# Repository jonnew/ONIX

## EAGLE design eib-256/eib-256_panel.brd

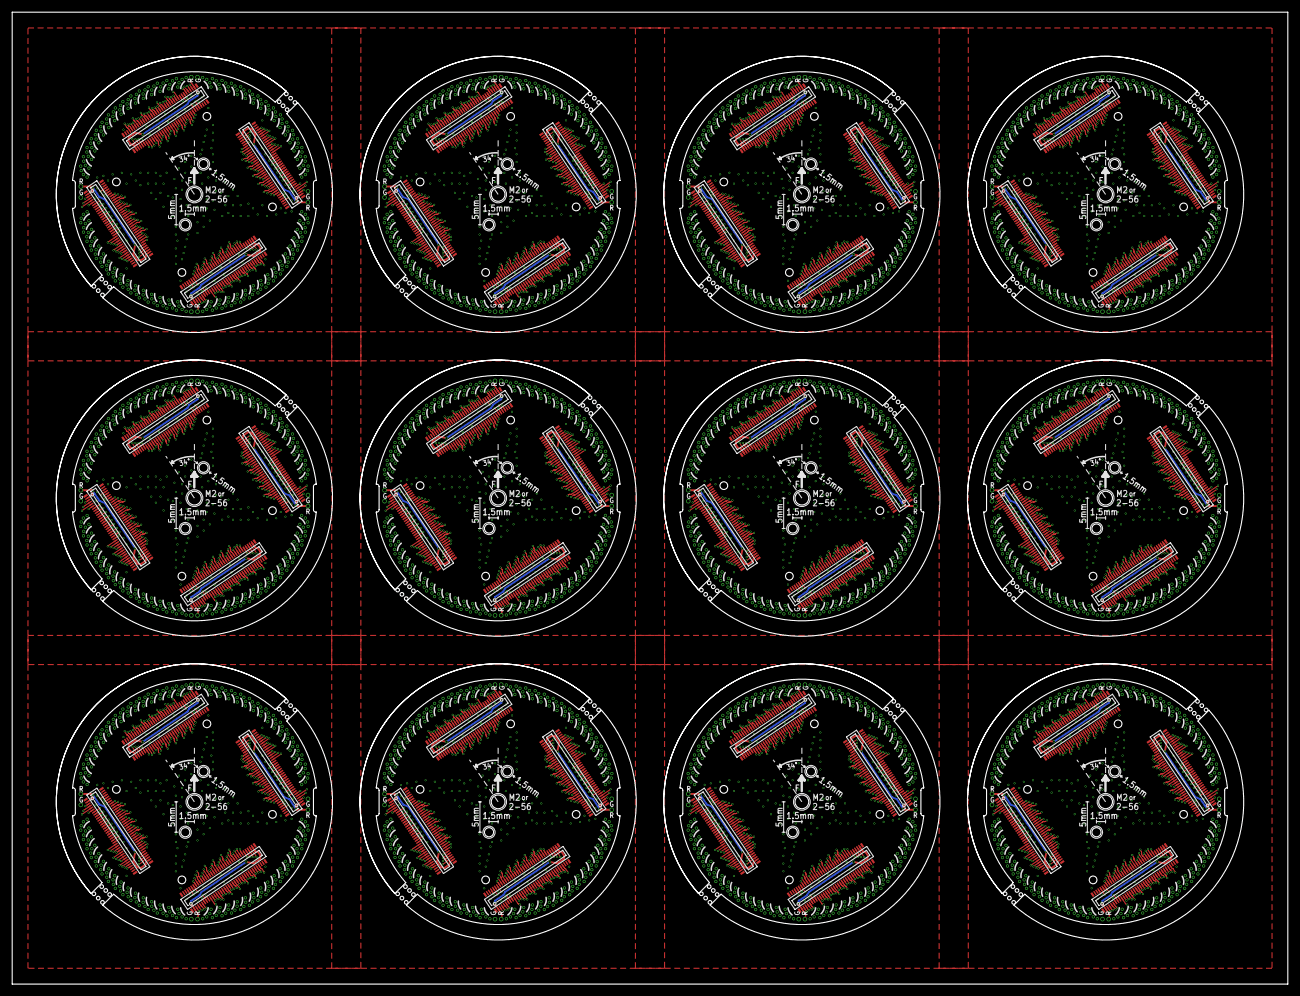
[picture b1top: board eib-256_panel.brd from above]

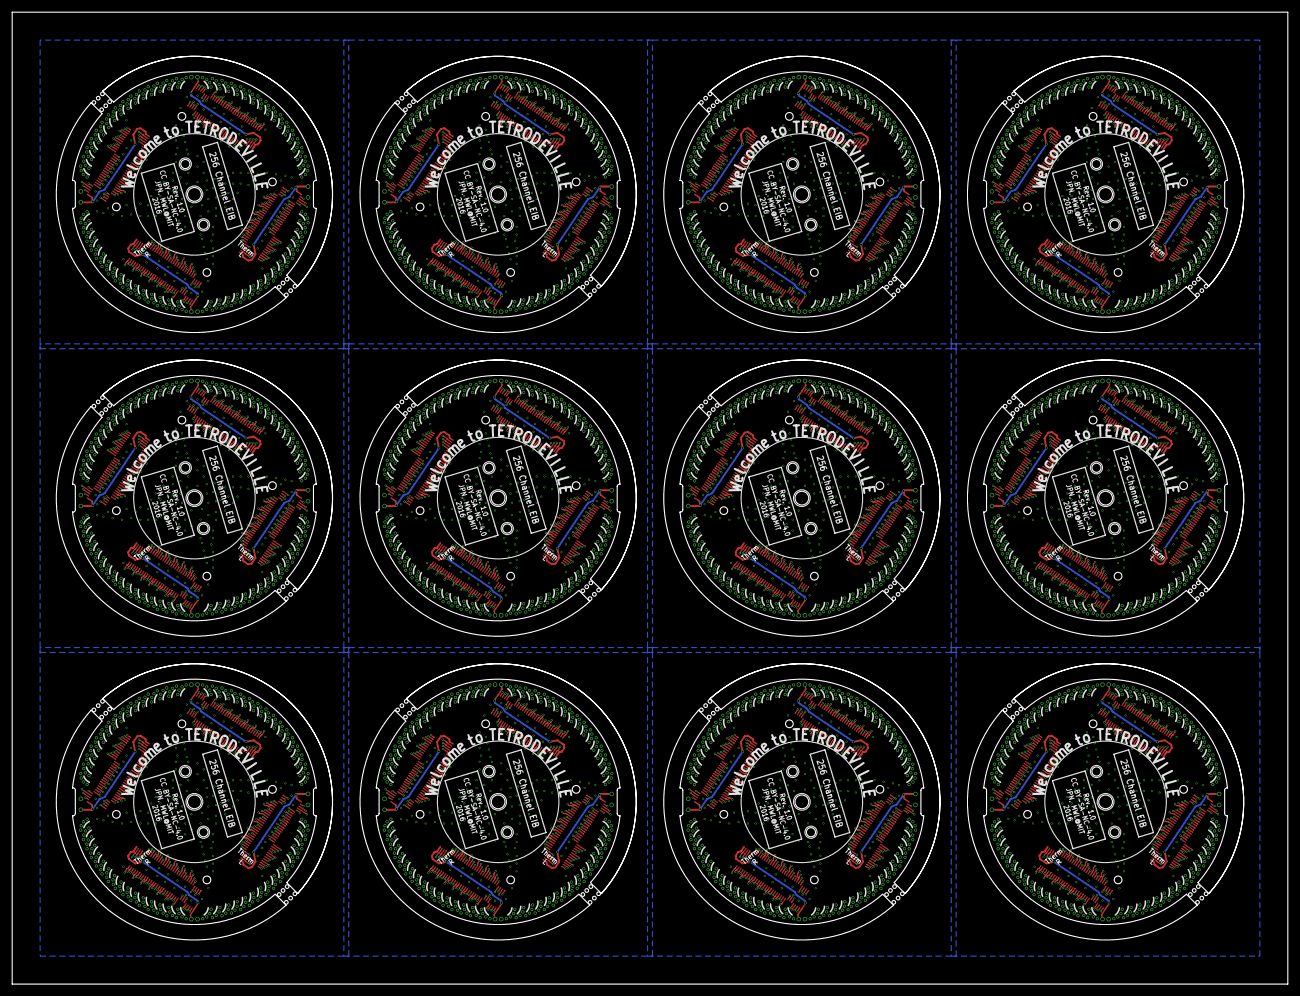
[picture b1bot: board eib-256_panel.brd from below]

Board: 4 copper layers, 210.0 x 160.0 mm, 924 parts (384 on the bottom side), 3132 nets.

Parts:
A, A1, A2, A3, A4, A5, A6, A7, A8, A9, A10, A11: DF40HEAD; DF40-70HEAD
AGND_A, AGND_A1, AGND_A2, AGND_A3, AGND_A4, AGND_A5, AGND_A6, AGND_A7, AGND_A8, AGND_A9, AGND_A10, AGND_A11: LRG_GP; GOLDPIN_0.5ID_0.7OD
AGND_B, AGND_B1, AGND_B2, AGND_B3, AGND_B4, AGND_B5, AGND_B6, AGND_B7, AGND_B8, AGND_B9, AGND_B10, AGND_B11: LRG_GP; GOLDPIN_0.5ID_0.7OD
B, B1, B2, B3, B4, B5, B6, B7, B8, B9, B10, B11: DF40HEAD; DF40-70HEAD
C, C1, C2, C3, C4, C5, C6, C7, C8, C9, C10, C11: DF40HEAD; DF40-70HEAD
D, D1, D2, D3, D4, D5, D6, D7, D8, D9, D10, D11: DF40HEAD; DF40-70HEAD
REF_A0, REF_A1, REF_A2, REF_A3, REF_A4, REF_A5, REF_A6, REF_A7, REF_A8, REF_A9, REF_A10, REF_A11: LRG_GP; GOLDPIN_0.5ID_0.7OD
REF_B, REF_B1, REF_B2, REF_B3, REF_B4, REF_B5, REF_B6, REF_B7, REF_B8, REF_B9, REF_B10, REF_B11: LRG_GP; GOLDPIN_0.5ID_0.7OD
REF_C, REF_C1, REF_C2, REF_C3, REF_C4, REF_C5, REF_C6, REF_C7, REF_C8, REF_C9, REF_C10, REF_C11: LRG_GP; GOLDPIN_0.5ID_0.7OD
REF_D, REF_D1, REF_D2, REF_D3, REF_D4, REF_D5, REF_D6, REF_D7, REF_D8, REF_D9, REF_D10, REF_D11: LRG_GP; GOLDPIN_0.5ID_0.7OD
SHLD_C, SHLD_C1, SHLD_C2, SHLD_C3, SHLD_C4, SHLD_C5, SHLD_C6, SHLD_C7, SHLD_C8, SHLD_C9, SHLD_C10, SHLD_C11: LRG_GP; GOLDPIN_0.5ID_0.7OD
SHLD_D, SHLD_D1, SHLD_D2, SHLD_D3, SHLD_D4, SHLD_D5, SHLD_D6, SHLD_D7, SHLD_D8, SHLD_D9, SHLD_D10, SHLD_D11: LRG_GP; GOLDPIN_0.5ID_0.7OD
TET0, TET64, TET128, TET192, TET256, TET320, TET384, TET448, TET512, TET576, TET640, TET704: 0; TETRODE_0.3ID_LINEAR
TET1, TET65, TET129, TET193, TET257, TET321, TET385, TET449, TET513, TET577, TET641, TET705: 1; TETRODE_0.3ID_LINEAR
TET2, TET66, TET130, TET194, TET258, TET322, TET386, TET450, TET514, TET578, TET642, TET706: 2; TETRODE_0.3ID_LINEAR
TET3, TET67, TET131, TET195, TET259, TET323, TET387, TET451, TET515, TET579, TET643, TET707: 3; TETRODE_0.3ID_LINEAR
TET4, TET68, TET132, TET196, TET260, TET324, TET388, TET452, TET516, TET580, TET644, TET708: 4; TETRODE_0.3ID_LINEAR
TET5, TET69, TET133, TET197, TET261, TET325, TET389, TET453, TET517, TET581, TET645, TET709: 5; TETRODE_0.3ID_LINEAR
TET6, TET70, TET134, TET198, TET262, TET326, TET390, TET454, TET518, TET582, TET646, TET710: 6; TETRODE_0.3ID_LINEAR
TET7, TET71, TET135, TET199, TET263, TET327, TET391, TET455, TET519, TET583, TET647, TET711: 7; TETRODE_0.3ID_LINEAR
TET8, TET72, TET136, TET200, TET264, TET328, TET392, TET456, TET520, TET584, TET648, TET712: 8; TETRODE_0.3ID_LINEAR
TET9, TET73, TET137, TET201, TET265, TET329, TET393, TET457, TET521, TET585, TET649, TET713: 9; TETRODE_0.3ID_LINEAR
TET10, TET74, TET138, TET202, TET266, TET330, TET394, TET458, TET522, TET586, TET650, TET714: 10; TETRODE_0.3ID_LINEAR
TET11, TET75, TET139, TET203, TET267, TET331, TET395, TET459, TET523, TET587, TET651, TET715: 11; TETRODE_0.3ID_LINEAR
TET12, TET76, TET140, TET204, TET268, TET332, TET396, TET460, TET524, TET588, TET652, TET716: 12; TETRODE_0.3ID_LINEAR
TET13, TET77, TET141, TET205, TET269, TET333, TET397, TET461, TET525, TET589, TET653, TET717: 13; TETRODE_0.3ID_LINEAR
TET14, TET78, TET142, TET206, TET270, TET334, TET398, TET462, TET526, TET590, TET654, TET718: 14; TETRODE_0.3ID_LINEAR
TET15, TET79, TET143, TET207, TET271, TET335, TET399, TET463, TET527, TET591, TET655, TET719: 15; TETRODE_0.3ID_LINEAR
TET16, TET112, TET176, TET240, TET304, TET368, TET432, TET496, TET560, TET624, TET688, TET752: 16; TETRODE_0.3ID_LINEAR
TET17, TET113, TET177, TET241, TET305, TET369, TET433, TET497, TET561, TET625, TET689, TET753: 17; TETRODE_0.3ID_LINEAR
TET18, TET114, TET178, TET242, TET306, TET370, TET434, TET498, TET562, TET626, TET690, TET754: 18; TETRODE_0.3ID_LINEAR
TET19, TET115, TET179, TET243, TET307, TET371, TET435, TET499, TET563, TET627, TET691, TET755: 19; TETRODE_0.3ID_LINEAR
TET20, TET116, TET180, TET244, TET308, TET372, TET436, TET500, TET564, TET628, TET692, TET756: 20; TETRODE_0.3ID_LINEAR
TET21, TET117, TET181, TET245, TET309, TET373, TET437, TET501, TET565, TET629, TET693, TET757: 21; TETRODE_0.3ID_LINEAR
TET22, TET118, TET182, TET246, TET310, TET374, TET438, TET502, TET566, TET630, TET694, TET758: 22; TETRODE_0.3ID_LINEAR
TET23, TET119, TET183, TET247, TET311, TET375, TET439, TET503, TET567, TET631, TET695, TET759: 23; TETRODE_0.3ID_LINEAR
TET24, TET120, TET184, TET248, TET312, TET376, TET440, TET504, TET568, TET632, TET696, TET760: 24; TETRODE_0.3ID_LINEAR
TET25, TET121, TET185, TET249, TET313, TET377, TET441, TET505, TET569, TET633, TET697, TET761: 25; TETRODE_0.3ID_LINEAR
TET26, TET122, TET186, TET250, TET314, TET378, TET442, TET506, TET570, TET634, TET698, TET762: 26; TETRODE_0.3ID_LINEAR
TET27, TET123, TET187, TET251, TET315, TET379, TET443, TET507, TET571, TET635, TET699, TET763: 27; TETRODE_0.3ID_LINEAR
TET28, TET124, TET188, TET252, TET316, TET380, TET444, TET508, TET572, TET636, TET700, TET764: 28; TETRODE_0.3ID_LINEAR
TET29, TET125, TET189, TET253, TET317, TET381, TET445, TET509, TET573, TET637, TET701, TET765: 29; TETRODE_0.3ID_LINEAR
TET30, TET126, TET190, TET254, TET318, TET382, TET446, TET510, TET574, TET638, TET702, TET766: 30; TETRODE_0.3ID_LINEAR
TET31, TET127, TET191, TET255, TET319, TET383, TET447, TET511, TET575, TET639, TET703, TET767: 31; TETRODE_0.3ID_LINEAR
TET32, TET96, TET160, TET224, TET288, TET352, TET416, TET480, TET544, TET608, TET672, TET736: 32; TETRODE_0.3ID_LINEAR
TET33, TET97, TET161, TET225, TET289, TET353, TET417, TET481, TET545, TET609, TET673, TET737: 33; TETRODE_0.3ID_LINEAR
TET34, TET98, TET162, TET226, TET290, TET354, TET418, TET482, TET546, TET610, TET674, TET738: 34; TETRODE_0.3ID_LINEAR
TET35, TET99, TET163, TET227, TET291, TET355, TET419, TET483, TET547, TET611, TET675, TET739: 35; TETRODE_0.3ID_LINEAR
TET36, TET100, TET164, TET228, TET292, TET356, TET420, TET484, TET548, TET612, TET676, TET740: 36; TETRODE_0.3ID_LINEAR
TET37, TET101, TET165, TET229, TET293, TET357, TET421, TET485, TET549, TET613, TET677, TET741: 37; TETRODE_0.3ID_LINEAR
TET38, TET102, TET166, TET230, TET294, TET358, TET422, TET486, TET550, TET614, TET678, TET742: 38; TETRODE_0.3ID_LINEAR
TET39, TET103, TET167, TET231, TET295, TET359, TET423, TET487, TET551, TET615, TET679, TET743: 39; TETRODE_0.3ID_LINEAR
TET40, TET104, TET168, TET232, TET296, TET360, TET424, TET488, TET552, TET616, TET680, TET744: 40; TETRODE_0.3ID_LINEAR
TET41, TET105, TET169, TET233, TET297, TET361, TET425, TET489, TET553, TET617, TET681, TET745: 41; TETRODE_0.3ID_LINEAR
TET42, TET106, TET170, TET234, TET298, TET362, TET426, TET490, TET554, TET618, TET682, TET746: 42; TETRODE_0.3ID_LINEAR
TET43, TET107, TET171, TET235, TET299, TET363, TET427, TET491, TET555, TET619, TET683, TET747: 43; TETRODE_0.3ID_LINEAR
TET44, TET108, TET172, TET236, TET300, TET364, TET428, TET492, TET556, TET620, TET684, TET748: 44; TETRODE_0.3ID_LINEAR
TET45, TET109, TET173, TET237, TET301, TET365, TET429, TET493, TET557, TET621, TET685, TET749: 45; TETRODE_0.3ID_LINEAR
TET46, TET110, TET174, TET238, TET302, TET366, TET430, TET494, TET558, TET622, TET686, TET750: 46; TETRODE_0.3ID_LINEAR
TET47, TET111, TET175, TET239, TET303, TET367, TET431, TET495, TET559, TET623, TET687, TET751: 47; TETRODE_0.3ID_LINEAR
TET48, TET80, TET144, TET208, TET272, TET336, TET400, TET464, TET528, TET592, TET656, TET720: 48; TETRODE_0.3ID_LINEAR
TET49, TET81, TET145, TET209, TET273, TET337, TET401, TET465, TET529, TET593, TET657, TET721: 49; TETRODE_0.3ID_LINEAR
TET50, TET82, TET146, TET210, TET274, TET338, TET402, TET466, TET530, TET594, TET658, TET722: 50; TETRODE_0.3ID_LINEAR
TET51, TET83, TET147, TET211, TET275, TET339, TET403, TET467, TET531, TET595, TET659, TET723: 51; TETRODE_0.3ID_LINEAR
TET52, TET84, TET148, TET212, TET276, TET340, TET404, TET468, TET532, TET596, TET660, TET724: 52; TETRODE_0.3ID_LINEAR
TET53, TET85, TET149, TET213, TET277, TET341, TET405, TET469, TET533, TET597, TET661, TET725: 53; TETRODE_0.3ID_LINEAR
TET54, TET86, TET150, TET214, TET278, TET342, TET406, TET470, TET534, TET598, TET662, TET726: 54; TETRODE_0.3ID_LINEAR
TET55, TET87, TET151, TET215, TET279, TET343, TET407, TET471, TET535, TET599, TET663, TET727: 55; TETRODE_0.3ID_LINEAR
TET56, TET88, TET152, TET216, TET280, TET344, TET408, TET472, TET536, TET600, TET664, TET728: 56; TETRODE_0.3ID_LINEAR
TET57, TET89, TET153, TET217, TET281, TET345, TET409, TET473, TET537, TET601, TET665, TET729: 57; TETRODE_0.3ID_LINEAR
TET58, TET90, TET154, TET218, TET282, TET346, TET410, TET474, TET538, TET602, TET666, TET730: 58; TETRODE_0.3ID_LINEAR
TET59, TET91, TET155, TET219, TET283, TET347, TET411, TET475, TET539, TET603, TET667, TET731: 59; TETRODE_0.3ID_LINEAR
TET60, TET92, TET156, TET220, TET284, TET348, TET412, TET476, TET540, TET604, TET668, TET732: 60; TETRODE_0.3ID_LINEAR
TET61, TET93, TET157, TET221, TET285, TET349, TET413, TET477, TET541, TET605, TET669, TET733: 61; TETRODE_0.3ID_LINEAR
TET62, TET94, TET158, TET222, TET286, TET350, TET414, TET478, TET542, TET606, TET670, TET734: 62; TETRODE_0.3ID_LINEAR
TET63, TET95, TET159, TET223, TET287, TET351, TET415, TET479, TET543, TET607, TET671, TET735: 63; TETRODE_0.3ID_LINEAR
U$1, U$2, U$3, U$4, U$5, U$6, U$7, U$8, U$9, U$10, U$11, U$12: EIB_MOUNT_A

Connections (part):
GND: A.34, A.35, A.69, A.70, A.M1, A.M2, A.M3, A.M4, AGND_A.P$1, AGND_B.P$1, B.34, B.35, B.69, B.70, B.M1, B.M2, B.M3, B.M4, C.34, C.35, C.69, C.70, C.M1, C.M2, C.M3, C.M4, D.34, D.35, D.69, D.70, D.M1, D.M2, D.M3, D.M4, SHLD_C.P$1, SHLD_D.P$1
GND1: A1.34, A1.35, A1.69, A1.70, A1.M1, A1.M2, A1.M3, A1.M4, AGND_A1.P$1, AGND_B1.P$1, B1.34, B1.35, B1.69, B1.70, B1.M1, B1.M2, B1.M3, B1.M4, C1.34, C1.35, C1.69, C1.70, C1.M1, C1.M2, C1.M3, C1.M4, D1.34, D1.35, D1.69, D1.70, D1.M1, D1.M2, D1.M3, D1.M4, SHLD_C1.P$1, SHLD_D1.P$1
GND2: A2.34, A2.35, A2.69, A2.70, A2.M1, A2.M2, A2.M3, A2.M4, AGND_A2.P$1, AGND_B2.P$1, B2.34, B2.35, B2.69, B2.70, B2.M1, B2.M2, B2.M3, B2.M4, C2.34, C2.35, C2.69, C2.70, C2.M1, C2.M2, C2.M3, C2.M4, D2.34, D2.35, D2.69, D2.70, D2.M1, D2.M2, D2.M3, D2.M4, SHLD_C2.P$1, SHLD_D2.P$1
GND3: A3.34, A3.35, A3.69, A3.70, A3.M1, A3.M2, A3.M3, A3.M4, AGND_A3.P$1, AGND_B3.P$1, B3.34, B3.35, B3.69, B3.70, B3.M1, B3.M2, B3.M3, B3.M4, C3.34, C3.35, C3.69, C3.70, C3.M1, C3.M2, C3.M3, C3.M4, D3.34, D3.35, D3.69, D3.70, D3.M1, D3.M2, D3.M3, D3.M4, SHLD_C3.P$1, SHLD_D3.P$1
GND4: A4.34, A4.35, A4.69, A4.70, A4.M1, A4.M2, A4.M3, A4.M4, AGND_A4.P$1, AGND_B4.P$1, B4.34, B4.35, B4.69, B4.70, B4.M1, B4.M2, B4.M3, B4.M4, C4.34, C4.35, C4.69, C4.70, C4.M1, C4.M2, C4.M3, C4.M4, D4.34, D4.35, D4.69, D4.70, D4.M1, D4.M2, D4.M3, D4.M4, SHLD_C4.P$1, SHLD_D4.P$1
GND5: A5.34, A5.35, A5.69, A5.70, A5.M1, A5.M2, A5.M3, A5.M4, AGND_A5.P$1, AGND_B5.P$1, B5.34, B5.35, B5.69, B5.70, B5.M1, B5.M2, B5.M3, B5.M4, C5.34, C5.35, C5.69, C5.70, C5.M1, C5.M2, C5.M3, C5.M4, D5.34, D5.35, D5.69, D5.70, D5.M1, D5.M2, D5.M3, D5.M4, SHLD_C5.P$1, SHLD_D5.P$1
GND6: A6.34, A6.35, A6.69, A6.70, A6.M1, A6.M2, A6.M3, A6.M4, AGND_A6.P$1, AGND_B6.P$1, B6.34, B6.35, B6.69, B6.70, B6.M1, B6.M2, B6.M3, B6.M4, C6.34, C6.35, C6.69, C6.70, C6.M1, C6.M2, C6.M3, C6.M4, D6.34, D6.35, D6.69, D6.70, D6.M1, D6.M2, D6.M3, D6.M4, SHLD_C6.P$1, SHLD_D6.P$1
GND7: A7.34, A7.35, A7.69, A7.70, A7.M1, A7.M2, A7.M3, A7.M4, AGND_A7.P$1, AGND_B7.P$1, B7.34, B7.35, B7.69, B7.70, B7.M1, B7.M2, B7.M3, B7.M4, C7.34, C7.35, C7.69, C7.70, C7.M1, C7.M2, C7.M3, C7.M4, D7.34, D7.35, D7.69, D7.70, D7.M1, D7.M2, D7.M3, D7.M4, SHLD_C7.P$1, SHLD_D7.P$1
GND8: A8.34, A8.35, A8.69, A8.70, A8.M1, A8.M2, A8.M3, A8.M4, AGND_A8.P$1, AGND_B8.P$1, B8.34, B8.35, B8.69, B8.70, B8.M1, B8.M2, B8.M3, B8.M4, C8.34, C8.35, C8.69, C8.70, C8.M1, C8.M2, C8.M3, C8.M4, D8.34, D8.35, D8.69, D8.70, D8.M1, D8.M2, D8.M3, D8.M4, SHLD_C8.P$1, SHLD_D8.P$1
GND9: A9.34, A9.35, A9.69, A9.70, A9.M1, A9.M2, A9.M3, A9.M4, AGND_A9.P$1, AGND_B9.P$1, B9.34, B9.35, B9.69, B9.70, B9.M1, B9.M2, B9.M3, B9.M4, C9.34, C9.35, C9.69, C9.70, C9.M1, C9.M2, C9.M3, C9.M4, D9.34, D9.35, D9.69, D9.70, D9.M1, D9.M2, D9.M3, D9.M4, SHLD_C9.P$1, SHLD_D9.P$1
GND10: A10.34, A10.35, A10.69, A10.70, A10.M1, A10.M2, A10.M3, A10.M4, AGND_A10.P$1, AGND_B10.P$1, B10.34, B10.35, B10.69, B10.70, B10.M1, B10.M2, B10.M3, B10.M4, C10.34, C10.35, C10.69, C10.70, C10.M1, C10.M2, C10.M3, C10.M4, D10.34, D10.35, D10.69, D10.70, D10.M1, D10.M2, D10.M3, D10.M4, SHLD_C10.P$1, SHLD_D10.P$1
GND11: A11.34, A11.35, A11.69, A11.70, A11.M1, A11.M2, A11.M3, A11.M4, AGND_A11.P$1, AGND_B11.P$1, B11.34, B11.35, B11.69, B11.70, B11.M1, B11.M2, B11.M3, B11.M4, C11.34, C11.35, C11.69, C11.70, C11.M1, C11.M2, C11.M3, C11.M4, D11.34, D11.35, D11.69, D11.70, D11.M1, D11.M2, D11.M3, D11.M4, SHLD_C11.P$1, SHLD_D11.P$1
unnamed: D.2, TET48.0
unnamed: D.3, TET48.1
unnamed: D.4, TET48.2
unnamed: D.5, TET48.3
unnamed: D.6, TET49.0
unnamed: D.7, TET49.1
unnamed: D.8, TET49.2
unnamed: D.9, TET49.3
unnamed: D.10, TET50.0
unnamed: D.11, TET50.1
unnamed: D.12, TET50.2
unnamed: D.13, TET50.3
unnamed: D.14, TET51.0
unnamed: D.15, TET51.1
unnamed: D.16, TET51.2
unnamed: D.17, TET51.3
unnamed: D.18, TET52.0
unnamed: D.19, TET52.1
unnamed: D.20, TET52.2
unnamed: D.21, TET52.3
unnamed: D.22, TET53.0
unnamed: D.23, TET53.1
unnamed: D.24, TET53.2
unnamed: D.25, TET53.3
unnamed: D.26, TET54.0
unnamed: D.27, TET54.1
unnamed: D.28, TET54.2
unnamed: D.29, TET54.3
unnamed: D.30, TET55.0
unnamed: D.31, TET55.1
unnamed: D.32, TET55.2
unnamed: D.42, TET57.1
unnamed: D.43, TET57.2
unnamed: D.44, TET57.3
unnamed: D.45, TET58.0
unnamed: D.46, TET58.1
unnamed: D.47, TET58.2
unnamed: D.48, TET58.3
unnamed: D.49, TET59.0
unnamed: D.50, TET59.1
unnamed: D.51, TET59.2
unnamed: D.52, TET59.3
unnamed: D.53, TET60.0
unnamed: D.54, TET60.1
unnamed: D.55, TET60.2
unnamed: D.56, TET60.3
unnamed: D.57, TET61.0
unnamed: D.58, TET61.1
unnamed: D.59, TET61.2
unnamed: D.60, TET61.3
unnamed: D.61, TET62.0
unnamed: D.62, TET62.1
unnamed: D.63, TET62.2
unnamed: D.64, TET62.3
unnamed: D.65, TET63.0
unnamed: D.66, TET63.1
unnamed: D.67, TET63.2
unnamed: D.68, TET63.3
unnamed: D.41, TET57.0
unnamed: D.40, TET56.3
unnamed: D.39, TET56.2
unnamed: D.38, TET56.1
unnamed: D.33, TET55.3
unnamed: D.37, TET56.0
unnamed: C.3, TET16.1
unnamed: C.2, TET16.0
unnamed: C.32, TET23.2
unnamed: C.33, TET23.3
unnamed: C.28, TET22.2
unnamed: C.29, TET22.3
unnamed: C.24, TET21.2
unnamed: C.25, TET21.3
unnamed: C.20, TET20.2
unnamed: C.21, TET20.3
unnamed: C.16, TET19.2
unnamed: C.17, TET19.3
unnamed: C.12, TET18.2
unnamed: C.13, TET18.3
unnamed: C.8, TET17.2
unnamed: C.9, TET17.3
unnamed: C.66, TET31.1
unnamed: C.65, TET31.0
unnamed: C.62, TET30.1
unnamed: C.64, TET30.3
unnamed: C.58, TET29.1
unnamed: C.57, TET29.0
unnamed: C.54, TET28.1
unnamed: C.53, TET28.0
unnamed: C.49, TET27.0
unnamed: C.50, TET27.1
unnamed: C.46, TET26.1
unnamed: C.45, TET26.0
unnamed: C.42, TET25.1
unnamed: C.41, TET25.0
unnamed: C.38, TET24.1
unnamed: C.37, TET24.0
unnamed: A1.33, TET71.0
unnamed: A1.32, TET71.1
unnamed: A1.31, TET71.2
unnamed: A1.30, TET71.3
unnamed: A1.29, TET70.0
unnamed: A1.28, TET70.1
unnamed: A1.27, TET70.2
unnamed: A1.26, TET70.3
unnamed: A1.25, TET69.0
unnamed: A1.24, TET69.1
unnamed: A1.23, TET69.2
unnamed: A1.22, TET69.3
unnamed: A1.21, TET68.0
unnamed: A1.20, TET68.1
unnamed: A1.19, TET68.2
unnamed: A1.18, TET68.3
unnamed: A1.17, TET67.0
unnamed: A1.16, TET67.1
unnamed: A1.15, TET67.2
unnamed: A1.14, TET67.3
unnamed: A1.13, TET66.0
unnamed: A1.12, TET66.1
unnamed: A1.11, TET66.2
unnamed: A1.10, TET66.3
unnamed: A1.9, TET65.0
unnamed: A1.8, TET65.1
unnamed: A1.7, TET65.2
unnamed: A1.6, TET65.3
unnamed: A1.5, TET64.0
unnamed: A1.4, TET64.1
unnamed: A1.3, TET64.2
unnamed: A1.38, TET72.2
unnamed: A1.39, TET72.1
unnamed: A1.40, TET72.0
unnamed: A1.41, TET73.3
unnamed: A1.42, TET73.2
unnamed: A1.43, TET73.1
unnamed: A1.44, TET73.0
unnamed: A1.45, TET74.3
unnamed: A1.46, TET74.2
unnamed: A1.47, TET74.1
unnamed: A1.48, TET74.0
unnamed: A1.49, TET75.3
unnamed: A1.50, TET75.2
unnamed: A1.51, TET75.1
unnamed: A1.52, TET75.0
unnamed: A1.53, TET76.3
unnamed: A1.54, TET76.2
unnamed: A1.55, TET76.1
unnamed: A1.56, TET76.0
unnamed: A1.57, TET77.3
unnamed: A1.58, TET77.2
unnamed: A1.59, TET77.1
unnamed: A1.60, TET77.0
unnamed: A1.61, TET78.3
unnamed: A1.62, TET78.2
unnamed: A1.63, TET78.1
unnamed: A1.64, TET78.0
unnamed: A1.65, TET79.3
unnamed: A1.66, TET79.2
unnamed: A1.67, TET79.1
unnamed: A1.68, TET79.0
unnamed: A1.2, TET64.3
unnamed: A1.37, TET72.3
unnamed: D1.2, TET80.0
unnamed: D1.3, TET80.1
unnamed: D1.4, TET80.2
unnamed: D1.5, TET80.3
unnamed: D1.6, TET81.0
unnamed: D1.7, TET81.1
unnamed: D1.8, TET81.2
unnamed: D1.9, TET81.3
unnamed: D1.10, TET82.0
unnamed: D1.11, TET82.1
unnamed: D1.12, TET82.2
unnamed: D1.13, TET82.3
unnamed: D1.14, TET83.0
unnamed: D1.15, TET83.1
unnamed: D1.16, TET83.2
unnamed: D1.17, TET83.3
unnamed: D1.18, TET84.0
unnamed: D1.19, TET84.1
unnamed: D1.20, TET84.2
unnamed: D1.21, TET84.3
unnamed: D1.22, TET85.0
unnamed: D1.23, TET85.1
unnamed: D1.24, TET85.2
unnamed: D1.25, TET85.3
unnamed: D1.26, TET86.0
unnamed: D1.27, TET86.1
unnamed: D1.28, TET86.2
unnamed: D1.29, TET86.3
unnamed: D1.30, TET87.0
unnamed: D1.31, TET87.1
unnamed: D1.32, TET87.2
unnamed: D1.33, TET87.3
unnamed: B.33, TET39.0
unnamed: B.32, TET39.1
unnamed: B.31, TET39.2
unnamed: B.30, TET39.3
unnamed: B.29, TET38.0
unnamed: B.28, TET38.1
unnamed: A.33, TET7.0
unnamed: A.32, TET7.1
unnamed: A.31, TET7.2
unnamed: A.30, TET7.3
unnamed: A.29, TET6.0
unnamed: A.28, TET6.1
unnamed: A.27, TET6.2
unnamed: A.26, TET6.3
unnamed: A.25, TET5.0
unnamed: A.24, TET5.1
unnamed: A.23, TET5.2
unnamed: A.22, TET5.3
unnamed: A.21, TET4.0
unnamed: A.20, TET4.1
unnamed: A.19, TET4.2
unnamed: A.18, TET4.3
unnamed: A.17, TET3.0
unnamed: A.16, TET3.1
unnamed: A.15, TET3.2
unnamed: A.14, TET3.3
unnamed: A.13, TET2.0
unnamed: A.12, TET2.1
unnamed: A.11, TET2.2
unnamed: A.10, TET2.3
unnamed: A.9, TET1.0
unnamed: A.8, TET1.1
unnamed: A.7, TET1.2
unnamed: A.6, TET1.3
unnamed: A.5, TET0.0
unnamed: A.4, TET0.1
unnamed: A.3, TET0.2
unnamed: A.2, TET0.3
unnamed: A.38, TET8.2
unnamed: A.39, TET8.1
unnamed: A.40, TET8.0
unnamed: A.41, TET9.3
unnamed: A.42, TET9.2
unnamed: A.43, TET9.1
unnamed: A.44, TET9.0
unnamed: A.45, TET10.3
unnamed: A.46, TET10.2
unnamed: A.47, TET10.1
unnamed: A.48, TET10.0
unnamed: A.49, TET11.3
unnamed: A.50, TET11.2
unnamed: A.51, TET11.1
unnamed: A.52, TET11.0
unnamed: A.53, TET12.3
unnamed: A.54, TET12.2
unnamed: A.55, TET12.1
unnamed: A.56, TET12.0
unnamed: A.57, TET13.3
unnamed: A.58, TET13.2
unnamed: A.59, TET13.1
unnamed: A.60, TET13.0
unnamed: A.61, TET14.3
unnamed: A.62, TET14.2
unnamed: A.63, TET14.1
unnamed: A.64, TET14.0
unnamed: A.65, TET15.3
unnamed: A.66, TET15.2
unnamed: A.67, TET15.1
unnamed: A.68, TET15.0
unnamed: B.27, TET38.2
unnamed: B.26, TET38.3
unnamed: B.25, TET37.0
unnamed: B.24, TET37.1
unnamed: B.23, TET37.2
unnamed: B.22, TET37.3
unnamed: B.21, TET36.0
unnamed: B.20, TET36.1
unnamed: B.19, TET36.2
unnamed: B.18, TET36.3
unnamed: B.17, TET35.0
unnamed: B.16, TET35.1
unnamed: B.15, TET35.2
unnamed: B.14, TET35.3
unnamed: B.13, TET34.0
unnamed: B.12, TET34.1
unnamed: B.11, TET34.2
unnamed: B.10, TET34.3
unnamed: B.9, TET33.0
unnamed: B.8, TET33.1
unnamed: B.7, TET33.2
unnamed: B.6, TET33.3
unnamed: B.5, TET32.0
unnamed: B.4, TET32.1
unnamed: B.3, TET32.2
unnamed: B.38, TET40.2
unnamed: B.39, TET40.1
unnamed: B.40, TET40.0
unnamed: B.41, TET41.3
unnamed: B.42, TET41.2
unnamed: B.43, TET41.1
unnamed: B.44, TET41.0
unnamed: B.45, TET42.3
unnamed: B.46, TET42.2
unnamed: B.47, TET42.1
unnamed: B.48, TET42.0
unnamed: B.49, TET43.3
unnamed: B.50, TET43.2
unnamed: B.51, TET43.1
unnamed: B.52, TET43.0
unnamed: B.53, TET44.3
unnamed: B.54, TET44.2
unnamed: B.55, TET44.1
unnamed: B.56, TET44.0
unnamed: B.57, TET45.3
unnamed: B.58, TET45.2
unnamed: B.59, TET45.1
unnamed: B.60, TET45.0
unnamed: B.61, TET46.3
unnamed: B.62, TET46.2
unnamed: B.63, TET46.1
unnamed: B.64, TET46.0
unnamed: B.65, TET47.3
unnamed: B.66, TET47.2
unnamed: B.67, TET47.1
unnamed: B.68, TET47.0
unnamed: B.2, TET32.3
unnamed: B.37, TET40.3
unnamed: D1.43, TET89.2
unnamed: D1.44, TET89.3
unnamed: C.4, TET16.2
unnamed: C.5, TET16.3
unnamed: C.6, TET17.0
unnamed: D1.45, TET90.0
unnamed: C.7, TET17.1
unnamed: D1.46, TET90.1
unnamed: C.10, TET18.0
unnamed: D1.47, TET90.2
unnamed: C.11, TET18.1
unnamed: D1.48, TET90.3
unnamed: C.14, TET19.0
unnamed: D1.49, TET91.0
unnamed: C.15, TET19.1
unnamed: D1.50, TET91.1
unnamed: C.18, TET20.0
unnamed: D1.51, TET91.2
unnamed: C.19, TET20.1
unnamed: D1.52, TET91.3
unnamed: C.22, TET21.0
unnamed: C.23, TET21.1
unnamed: D1.53, TET92.0
unnamed: D1.54, TET92.1
unnamed: D1.55, TET92.2
unnamed: C.27, TET22.1
unnamed: D1.56, TET92.3
unnamed: C.26, TET22.0
unnamed: C.30, TET23.0
unnamed: D1.57, TET93.0
unnamed: C.31, TET23.1
unnamed: D1.58, TET93.1
unnamed: C.43, TET25.2
unnamed: D1.59, TET93.2
unnamed: C.48, TET26.3
unnamed: D1.60, TET93.3
unnamed: C.47, TET26.2
unnamed: D1.61, TET94.0
unnamed: C.52, TET27.3
unnamed: D1.62, TET94.1
unnamed: C.51, TET27.2
unnamed: D1.63, TET94.2
unnamed: C.56, TET28.3
unnamed: D1.64, TET94.3
unnamed: C.55, TET28.2
unnamed: D1.65, TET95.0
unnamed: C.60, TET29.3
unnamed: D1.66, TET95.1
unnamed: C.59, TET29.2
unnamed: D1.67, TET95.2
unnamed: C.61, TET30.0
unnamed: D1.68, TET95.3
unnamed: C.63, TET30.2
unnamed: D1.42, TET89.1
unnamed: C.68, TET31.3
unnamed: D1.41, TET89.0
unnamed: C.67, TET31.2
unnamed: D1.40, TET88.3
unnamed: D1.39, TET88.2
unnamed: C.44, TET25.3
unnamed: D1.38, TET88.1
unnamed: D1.37, TET88.0
unnamed: C.39, TET24.2
unnamed: C.40, TET24.3
unnamed: B1.33, TET103.0
unnamed: B1.32, TET103.1
unnamed: B1.31, TET103.2
unnamed: B1.30, TET103.3
unnamed: B1.29, TET102.0
unnamed: B1.28, TET102.1
unnamed: B1.27, TET102.2
unnamed: B1.26, TET102.3
unnamed: B1.25, TET101.0
unnamed: B1.24, TET101.1
unnamed: B1.23, TET101.2
unnamed: B1.22, TET101.3
unnamed: B1.21, TET100.0
unnamed: B1.20, TET100.1
unnamed: B1.19, TET100.2
unnamed: B1.18, TET100.3
unnamed: B1.17, TET99.0
unnamed: B1.16, TET99.1
unnamed: B1.15, TET99.2
unnamed: B1.14, TET99.3
unnamed: B1.13, TET98.0
unnamed: B1.12, TET98.1
unnamed: B1.11, TET98.2
unnamed: B1.10, TET98.3
unnamed: B1.9, TET97.0
unnamed: B1.8, TET97.1
unnamed: B1.7, TET97.2
unnamed: B1.6, TET97.3
unnamed: B1.5, TET96.0
unnamed: B1.4, TET96.1
unnamed: B1.3, TET96.2
unnamed: B1.38, TET104.2
unnamed: B1.39, TET104.1
unnamed: B1.40, TET104.0
unnamed: B1.41, TET105.3
unnamed: B1.42, TET105.2
unnamed: B1.43, TET105.1
unnamed: B1.44, TET105.0
unnamed: B1.45, TET106.3
unnamed: B1.46, TET106.2
unnamed: B1.47, TET106.1
unnamed: B1.48, TET106.0
unnamed: B1.49, TET107.3
unnamed: B1.50, TET107.2
unnamed: B1.51, TET107.1
unnamed: B1.52, TET107.0
unnamed: B1.53, TET108.3
unnamed: B1.54, TET108.2
unnamed: B1.55, TET108.1
unnamed: B1.56, TET108.0
unnamed: B1.57, TET109.3
unnamed: B1.58, TET109.2
unnamed: B1.59, TET109.1
unnamed: B1.60, TET109.0
unnamed: B1.61, TET110.3
unnamed: B1.62, TET110.2
unnamed: B1.63, TET110.1
unnamed: B1.64, TET110.0
unnamed: B1.65, TET111.3
unnamed: B1.66, TET111.2
unnamed: B1.67, TET111.1
unnamed: B1.68, TET111.0
unnamed: B1.2, TET96.3
unnamed: B1.37, TET104.3
unnamed: C1.4, TET112.2
unnamed: C1.5, TET112.3
unnamed: C1.6, TET113.0
unnamed: C1.7, TET113.1
unnamed: C1.10, TET114.0
unnamed: C1.11, TET114.1
unnamed: C1.14, TET115.0
unnamed: C1.15, TET115.1
unnamed: C1.18, TET116.0
unnamed: C1.19, TET116.1
unnamed: C1.22, TET117.0
unnamed: C1.23, TET117.1
unnamed: C1.27, TET118.1
unnamed: C1.26, TET118.0
unnamed: C1.30, TET119.0
unnamed: C1.31, TET119.1
unnamed: C1.43, TET121.2
unnamed: C1.48, TET122.3
unnamed: C1.47, TET122.2
unnamed: C1.52, TET123.3
unnamed: C1.51, TET123.2
unnamed: C1.56, TET124.3
unnamed: C1.55, TET124.2
unnamed: C1.60, TET125.3
unnamed: C1.59, TET125.2
unnamed: C1.61, TET126.0
unnamed: C1.63, TET126.2
unnamed: C1.68, TET127.3
unnamed: C1.67, TET127.2
unnamed: C1.44, TET121.3
unnamed: C1.39, TET120.2
unnamed: C1.40, TET120.3
unnamed: C1.3, TET112.1
unnamed: C1.2, TET112.0
unnamed: C1.32, TET119.2
unnamed: C1.33, TET119.3
unnamed: C1.28, TET118.2
unnamed: C1.29, TET118.3
unnamed: C1.24, TET117.2
unnamed: C1.25, TET117.3
unnamed: C1.20, TET116.2
unnamed: C1.21, TET116.3
unnamed: C1.16, TET115.2
unnamed: C1.17, TET115.3
unnamed: C1.12, TET114.2
unnamed: C1.13, TET114.3
unnamed: C1.8, TET113.2
unnamed: C1.9, TET113.3
unnamed: C1.66, TET127.1
unnamed: C1.65, TET127.0
unnamed: C1.62, TET126.1
unnamed: C1.64, TET126.3
unnamed: C1.58, TET125.1
unnamed: C1.57, TET125.0
unnamed: C1.54, TET124.1
unnamed: C1.53, TET124.0
unnamed: C1.49, TET123.0
unnamed: C1.50, TET123.1
unnamed: C1.46, TET122.1
unnamed: C1.45, TET122.0
unnamed: C1.42, TET121.1
unnamed: C1.41, TET121.0
unnamed: C1.38, TET120.1
unnamed: C1.37, TET120.0
unnamed: A2.33, TET135.0
unnamed: A2.32, TET135.1
unnamed: A2.31, TET135.2
unnamed: A2.30, TET135.3
unnamed: A2.29, TET134.0
unnamed: A2.28, TET134.1
unnamed: A2.27, TET134.2
unnamed: A2.26, TET134.3
unnamed: A2.25, TET133.0
unnamed: A2.24, TET133.1
unnamed: A2.23, TET133.2
unnamed: A2.22, TET133.3
unnamed: A2.21, TET132.0
unnamed: A2.20, TET132.1
unnamed: A2.19, TET132.2
unnamed: A2.18, TET132.3
unnamed: A2.17, TET131.0
unnamed: A2.16, TET131.1
unnamed: A2.15, TET131.2
unnamed: A2.14, TET131.3
unnamed: A2.13, TET130.0
unnamed: A2.12, TET130.1
unnamed: A2.11, TET130.2
unnamed: A2.10, TET130.3
unnamed: A2.9, TET129.0
unnamed: A2.8, TET129.1
unnamed: A2.7, TET129.2
unnamed: A2.6, TET129.3
unnamed: A2.5, TET128.0
unnamed: A2.4, TET128.1
unnamed: A2.3, TET128.2
unnamed: A2.38, TET136.2
unnamed: A2.39, TET136.1
unnamed: A2.40, TET136.0
unnamed: A2.41, TET137.3
unnamed: A2.42, TET137.2
unnamed: A2.43, TET137.1
unnamed: A2.44, TET137.0
unnamed: A2.45, TET138.3
unnamed: A2.46, TET138.2
unnamed: A2.47, TET138.1
unnamed: A2.48, TET138.0
unnamed: A2.49, TET139.3
unnamed: A2.50, TET139.2
unnamed: A2.51, TET139.1
unnamed: A2.52, TET139.0
unnamed: A2.53, TET140.3
unnamed: A2.54, TET140.2
unnamed: A2.55, TET140.1
unnamed: A2.56, TET140.0
unnamed: A2.57, TET141.3
unnamed: A2.58, TET141.2
unnamed: A2.59, TET141.1
unnamed: A2.60, TET141.0
unnamed: A2.61, TET142.3
unnamed: A2.62, TET142.2
unnamed: A2.63, TET142.1
unnamed: A2.64, TET142.0
unnamed: A2.65, TET143.3
unnamed: A2.66, TET143.2
unnamed: A2.67, TET143.1
unnamed: A2.68, TET143.0
unnamed: A2.2, TET128.3
unnamed: A2.37, TET136.3
unnamed: D2.2, TET144.0
unnamed: D2.3, TET144.1
unnamed: D2.4, TET144.2
unnamed: D2.5, TET144.3
unnamed: D2.6, TET145.0
unnamed: D2.7, TET145.1
unnamed: D2.8, TET145.2
unnamed: D2.9, TET145.3
unnamed: D2.10, TET146.0
unnamed: D2.11, TET146.1
unnamed: D2.12, TET146.2
unnamed: D2.13, TET146.3
unnamed: D2.14, TET147.0
unnamed: D2.15, TET147.1
unnamed: D2.16, TET147.2
unnamed: D2.17, TET147.3
unnamed: D2.18, TET148.0
unnamed: D2.19, TET148.1
unnamed: D2.20, TET148.2
unnamed: D2.21, TET148.3
unnamed: D2.22, TET149.0
unnamed: D2.23, TET149.1
unnamed: D2.24, TET149.2
unnamed: D2.25, TET149.3
unnamed: D2.26, TET150.0
unnamed: D2.27, TET150.1
unnamed: D2.28, TET150.2
unnamed: D2.29, TET150.3
unnamed: D2.30, TET151.0
unnamed: D2.31, TET151.1
unnamed: D2.32, TET151.2
unnamed: D2.33, TET151.3
unnamed: D2.43, TET153.2
unnamed: D2.44, TET153.3
unnamed: D2.45, TET154.0
unnamed: D2.46, TET154.1
unnamed: D2.47, TET154.2
unnamed: D2.48, TET154.3
unnamed: D2.49, TET155.0
unnamed: D2.50, TET155.1
unnamed: D2.51, TET155.2
unnamed: D2.52, TET155.3
unnamed: D2.53, TET156.0
unnamed: D2.54, TET156.1
unnamed: D2.55, TET156.2
unnamed: D2.56, TET156.3
unnamed: D2.57, TET157.0
unnamed: D2.58, TET157.1
unnamed: D2.59, TET157.2
unnamed: D2.60, TET157.3
unnamed: D2.61, TET158.0
unnamed: D2.62, TET158.1
unnamed: D2.63, TET158.2
unnamed: D2.64, TET158.3
unnamed: D2.65, TET159.0
unnamed: D2.66, TET159.1
unnamed: D2.67, TET159.2
unnamed: D2.68, TET159.3
unnamed: D2.42, TET153.1
unnamed: D2.41, TET153.0
unnamed: D2.40, TET152.3
unnamed: D2.39, TET152.2
unnamed: D2.38, TET152.1
unnamed: D2.37, TET152.0
unnamed: B2.33, TET167.0
unnamed: B2.32, TET167.1
unnamed: B2.31, TET167.2
unnamed: B2.30, TET167.3
unnamed: B2.29, TET166.0
unnamed: B2.28, TET166.1
unnamed: B2.27, TET166.2
unnamed: B2.26, TET166.3
unnamed: B2.25, TET165.0
unnamed: B2.24, TET165.1
unnamed: B2.23, TET165.2
unnamed: B2.22, TET165.3
unnamed: B2.21, TET164.0
unnamed: B2.20, TET164.1
unnamed: B2.19, TET164.2
unnamed: B2.18, TET164.3
unnamed: B2.17, TET163.0
unnamed: B2.16, TET163.1
unnamed: B2.15, TET163.2
unnamed: B2.14, TET163.3
unnamed: B2.13, TET162.0
unnamed: B2.12, TET162.1
unnamed: B2.11, TET162.2
unnamed: B2.10, TET162.3
unnamed: B2.9, TET161.0
unnamed: B2.8, TET161.1
unnamed: B2.7, TET161.2
unnamed: B2.6, TET161.3
unnamed: B2.5, TET160.0
unnamed: B2.4, TET160.1
unnamed: B2.3, TET160.2
unnamed: B2.38, TET168.2
unnamed: B2.39, TET168.1
unnamed: B2.40, TET168.0
unnamed: B2.41, TET169.3
unnamed: B2.42, TET169.2
unnamed: B2.43, TET169.1
unnamed: B2.44, TET169.0
unnamed: B2.45, TET170.3
unnamed: B2.46, TET170.2
unnamed: B2.47, TET170.1
unnamed: B2.48, TET170.0
unnamed: B2.49, TET171.3
unnamed: B2.50, TET171.2
unnamed: B2.51, TET171.1
unnamed: B2.52, TET171.0
unnamed: B2.53, TET172.3
unnamed: B2.54, TET172.2
unnamed: B2.55, TET172.1
unnamed: B2.56, TET172.0
unnamed: B2.57, TET173.3
unnamed: B2.58, TET173.2
unnamed: B2.59, TET173.1
unnamed: B2.60, TET173.0
unnamed: B2.61, TET174.3
unnamed: B2.62, TET174.2
unnamed: B2.63, TET174.1
unnamed: B2.64, TET174.0
unnamed: B2.65, TET175.3
unnamed: B2.66, TET175.2
unnamed: B2.67, TET175.1
unnamed: B2.68, TET175.0
unnamed: B2.2, TET160.3
unnamed: B2.37, TET168.3
unnamed: C2.4, TET176.2
unnamed: C2.5, TET176.3
unnamed: C2.6, TET177.0
unnamed: C2.7, TET177.1
unnamed: C2.10, TET178.0
unnamed: C2.11, TET178.1
unnamed: C2.14, TET179.0
unnamed: C2.15, TET179.1
unnamed: C2.18, TET180.0
unnamed: C2.19, TET180.1
unnamed: C2.22, TET181.0
unnamed: C2.23, TET181.1
unnamed: C2.27, TET182.1
unnamed: C2.26, TET182.0
unnamed: C2.30, TET183.0
unnamed: C2.31, TET183.1
unnamed: C2.43, TET185.2
unnamed: C2.48, TET186.3
unnamed: C2.47, TET186.2
unnamed: C2.52, TET187.3
unnamed: C2.51, TET187.2
unnamed: C2.56, TET188.3
unnamed: C2.55, TET188.2
unnamed: C2.60, TET189.3
unnamed: C2.59, TET189.2
unnamed: C2.61, TET190.0
unnamed: C2.63, TET190.2
unnamed: C2.68, TET191.3
unnamed: C2.67, TET191.2
unnamed: C2.44, TET185.3
unnamed: C2.39, TET184.2
unnamed: C2.40, TET184.3
unnamed: C2.3, TET176.1
unnamed: C2.2, TET176.0
unnamed: C2.32, TET183.2
unnamed: C2.33, TET183.3
unnamed: C2.28, TET182.2
unnamed: C2.29, TET182.3
unnamed: C2.24, TET181.2
unnamed: C2.25, TET181.3
unnamed: C2.20, TET180.2
unnamed: C2.21, TET180.3
unnamed: C2.16, TET179.2
unnamed: C2.17, TET179.3
unnamed: C2.12, TET178.2
unnamed: C2.13, TET178.3
unnamed: C2.8, TET177.2
unnamed: C2.9, TET177.3
unnamed: C2.66, TET191.1
unnamed: C2.65, TET191.0
unnamed: C2.62, TET190.1
unnamed: C2.64, TET190.3
unnamed: C2.58, TET189.1
unnamed: C2.57, TET189.0
unnamed: C2.54, TET188.1
unnamed: C2.53, TET188.0
unnamed: C2.49, TET187.0
unnamed: C2.50, TET187.1
unnamed: C2.46, TET186.1
unnamed: C2.45, TET186.0
unnamed: C2.42, TET185.1
unnamed: C2.41, TET185.0
unnamed: C2.38, TET184.1
unnamed: C2.37, TET184.0
unnamed: A3.33, TET199.0
unnamed: A3.32, TET199.1
unnamed: A3.31, TET199.2
unnamed: A3.30, TET199.3
unnamed: A3.29, TET198.0
unnamed: A3.28, TET198.1
unnamed: A3.27, TET198.2
unnamed: A3.26, TET198.3
unnamed: A3.25, TET197.0
unnamed: A3.24, TET197.1
unnamed: A3.23, TET197.2
unnamed: A3.22, TET197.3
unnamed: A3.21, TET196.0
unnamed: A3.20, TET196.1
unnamed: A3.19, TET196.2
unnamed: A3.18, TET196.3
unnamed: A3.17, TET195.0
unnamed: A3.16, TET195.1
unnamed: A3.15, TET195.2
unnamed: A3.14, TET195.3
unnamed: A3.13, TET194.0
unnamed: A3.12, TET194.1
unnamed: A3.11, TET194.2
unnamed: A3.10, TET194.3
unnamed: A3.9, TET193.0
unnamed: A3.8, TET193.1
unnamed: A3.7, TET193.2
unnamed: A3.6, TET193.3
unnamed: A3.5, TET192.0
unnamed: A3.4, TET192.1
unnamed: A3.3, TET192.2
unnamed: A3.38, TET200.2
unnamed: A3.39, TET200.1
unnamed: A3.40, TET200.0
unnamed: A3.41, TET201.3
unnamed: A3.42, TET201.2
unnamed: A3.43, TET201.1
unnamed: A3.44, TET201.0
unnamed: A3.45, TET202.3
unnamed: A3.46, TET202.2
unnamed: A3.47, TET202.1
unnamed: A3.48, TET202.0
unnamed: A3.49, TET203.3
unnamed: A3.50, TET203.2
unnamed: A3.51, TET203.1
unnamed: A3.52, TET203.0
unnamed: A3.53, TET204.3
unnamed: A3.54, TET204.2
unnamed: A3.55, TET204.1
unnamed: A3.56, TET204.0
unnamed: A3.57, TET205.3
unnamed: A3.58, TET205.2
unnamed: A3.59, TET205.1
unnamed: A3.60, TET205.0
unnamed: A3.61, TET206.3
unnamed: A3.62, TET206.2
unnamed: A3.63, TET206.1
unnamed: A3.64, TET206.0
unnamed: A3.65, TET207.3
unnamed: A3.66, TET207.2
unnamed: A3.67, TET207.1
unnamed: A3.68, TET207.0
unnamed: A3.2, TET192.3
unnamed: A3.37, TET200.3
unnamed: D3.2, TET208.0
unnamed: D3.3, TET208.1
unnamed: D3.4, TET208.2
unnamed: D3.5, TET208.3
unnamed: D3.6, TET209.0
unnamed: D3.7, TET209.1
unnamed: D3.8, TET209.2
unnamed: D3.9, TET209.3
unnamed: D3.10, TET210.0
unnamed: D3.11, TET210.1
unnamed: D3.12, TET210.2
unnamed: D3.13, TET210.3
unnamed: D3.14, TET211.0
unnamed: D3.15, TET211.1
unnamed: D3.16, TET211.2
unnamed: D3.17, TET211.3
unnamed: D3.18, TET212.0
unnamed: D3.19, TET212.1
unnamed: D3.20, TET212.2
unnamed: D3.21, TET212.3
unnamed: D3.22, TET213.0
unnamed: D3.23, TET213.1
unnamed: D3.24, TET213.2
unnamed: D3.25, TET213.3
unnamed: D3.26, TET214.0
unnamed: D3.27, TET214.1
unnamed: D3.28, TET214.2
unnamed: D3.29, TET214.3
unnamed: D3.30, TET215.0
unnamed: D3.31, TET215.1
unnamed: D3.32, TET215.2
unnamed: D3.33, TET215.3
unnamed: D3.43, TET217.2
unnamed: D3.44, TET217.3
unnamed: D3.45, TET218.0
unnamed: D3.46, TET218.1
unnamed: D3.47, TET218.2
unnamed: D3.48, TET218.3
unnamed: D3.49, TET219.0
unnamed: D3.50, TET219.1
unnamed: D3.51, TET219.2
unnamed: D3.52, TET219.3
unnamed: D3.53, TET220.0
unnamed: D3.54, TET220.1
unnamed: D3.55, TET220.2
unnamed: D3.56, TET220.3
unnamed: D3.57, TET221.0
unnamed: D3.58, TET221.1
unnamed: D3.59, TET221.2
unnamed: D3.60, TET221.3
unnamed: D3.61, TET222.0
unnamed: D3.62, TET222.1
unnamed: D3.63, TET222.2
unnamed: D3.64, TET222.3
unnamed: D3.65, TET223.0
unnamed: D3.66, TET223.1
unnamed: D3.67, TET223.2
unnamed: D3.68, TET223.3
unnamed: D3.42, TET217.1
unnamed: D3.41, TET217.0
unnamed: D3.40, TET216.3
unnamed: D3.39, TET216.2
unnamed: D3.38, TET216.1
unnamed: D3.37, TET216.0
unnamed: B3.33, TET231.0
unnamed: B3.32, TET231.1
unnamed: B3.31, TET231.2
unnamed: B3.30, TET231.3
unnamed: B3.29, TET230.0
unnamed: B3.28, TET230.1
unnamed: B3.27, TET230.2
unnamed: B3.26, TET230.3
unnamed: B3.25, TET229.0
unnamed: B3.24, TET229.1
unnamed: B3.23, TET229.2
unnamed: B3.22, TET229.3
unnamed: B3.21, TET228.0
unnamed: B3.20, TET228.1
unnamed: B3.19, TET228.2
unnamed: B3.18, TET228.3
unnamed: B3.17, TET227.0
unnamed: B3.16, TET227.1
unnamed: B3.15, TET227.2
unnamed: B3.14, TET227.3
unnamed: B3.13, TET226.0
unnamed: B3.12, TET226.1
unnamed: B3.11, TET226.2
unnamed: B3.10, TET226.3
unnamed: B3.9, TET225.0
unnamed: B3.8, TET225.1
unnamed: B3.7, TET225.2
unnamed: B3.6, TET225.3
unnamed: B3.5, TET224.0
unnamed: B3.4, TET224.1
unnamed: B3.3, TET224.2
unnamed: B3.38, TET232.2
unnamed: B3.39, TET232.1
unnamed: B3.40, TET232.0
unnamed: B3.41, TET233.3
unnamed: B3.42, TET233.2
unnamed: B3.43, TET233.1
unnamed: B3.44, TET233.0
unnamed: B3.45, TET234.3
unnamed: B3.46, TET234.2
unnamed: B3.47, TET234.1
unnamed: B3.48, TET234.0
unnamed: B3.49, TET235.3
unnamed: B3.50, TET235.2
unnamed: B3.51, TET235.1
unnamed: B3.52, TET235.0
unnamed: B3.53, TET236.3
unnamed: B3.54, TET236.2
unnamed: B3.55, TET236.1
unnamed: B3.56, TET236.0
unnamed: B3.57, TET237.3
unnamed: B3.58, TET237.2
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
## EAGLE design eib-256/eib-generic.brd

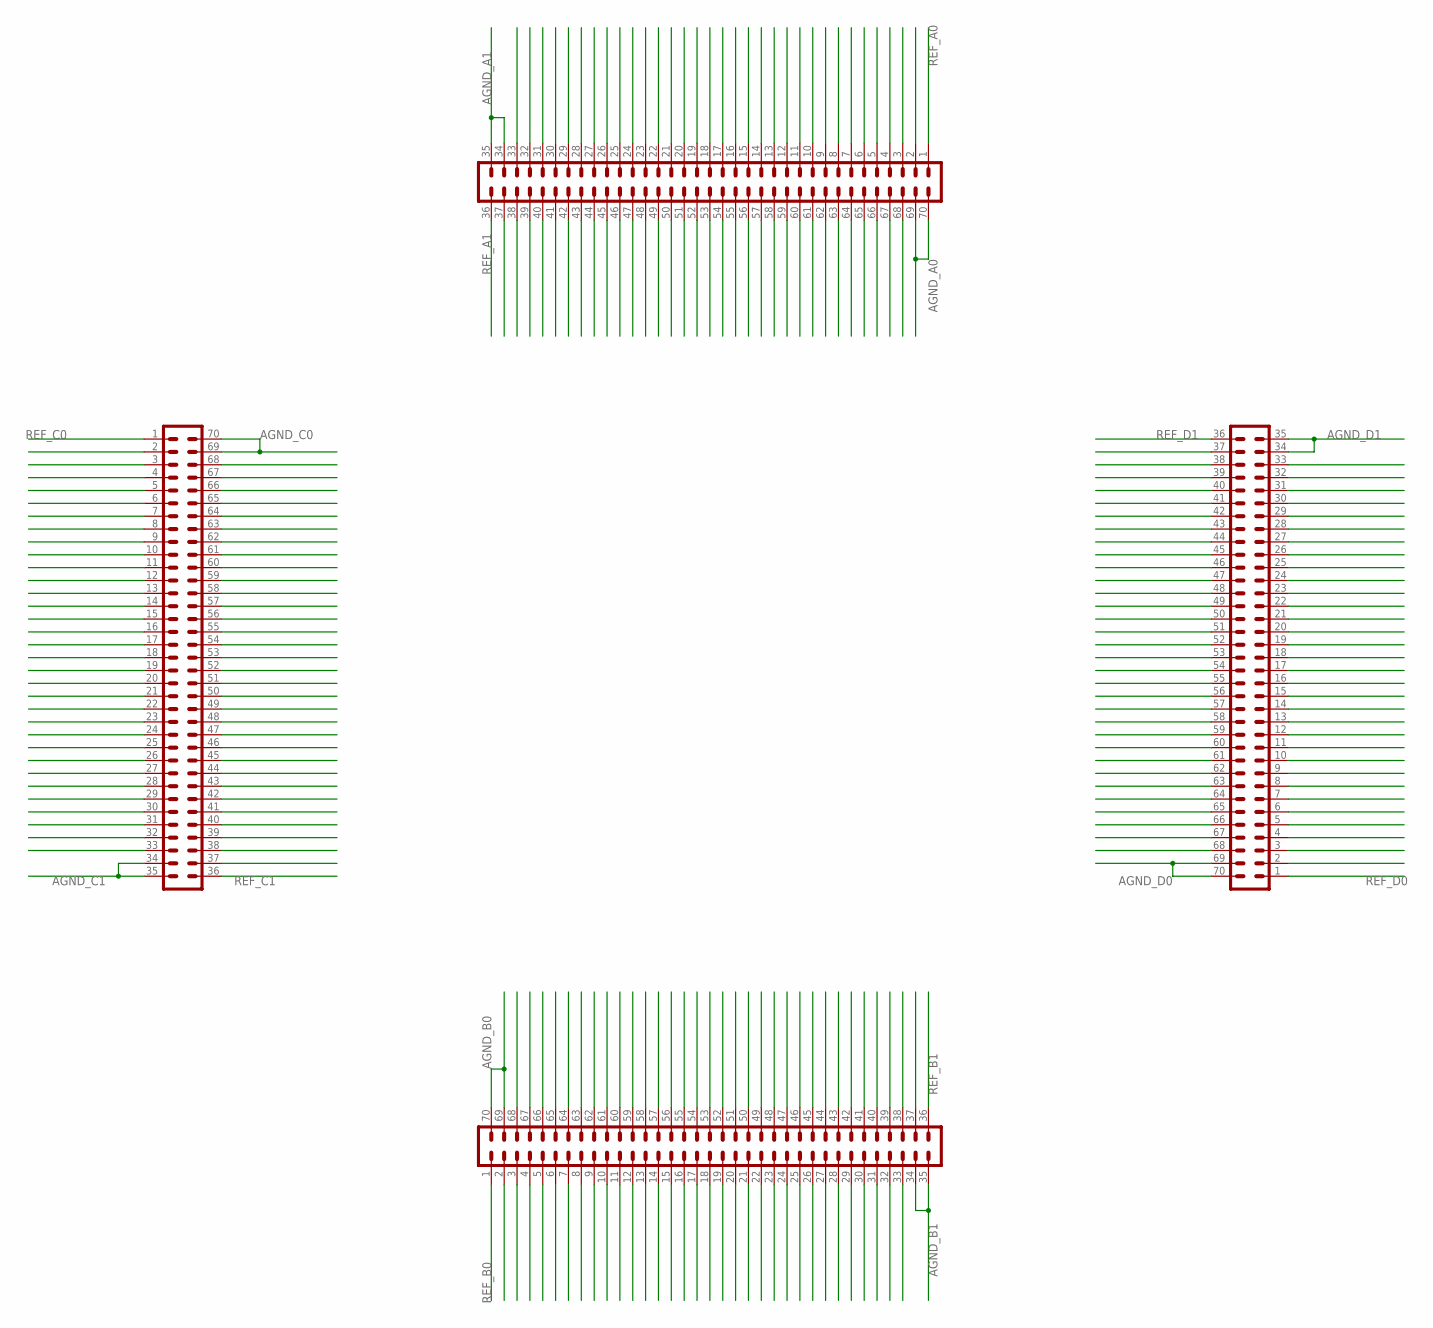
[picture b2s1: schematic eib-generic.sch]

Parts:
A: DF40HEAD; DF40-70HEAD
B: DF40HEAD; DF40-70HEAD
C: DF40HEAD; DF40-70HEAD
D: DF40HEAD; DF40-70HEAD

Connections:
AGND_A0: A.69, A.70
AGND_A1: A.34, A.35
AGND_B0: B.69, B.70
AGND_B1: B.34, B.35
AGND_C0: C.69, C.70
AGND_C1: C.34, C.35
AGND_D0: D.69, D.70
AGND_D1: D.34, D.35
REF_A0: A.1
REF_A1: A.36
REF_B0: B.1
REF_B1: B.36
REF_C0: C.1
REF_C1: C.36
REF_D0: D.1
REF_D1: D.36

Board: 4 copper layers, 4 parts (0 on the bottom side), 8 nets, no tracks yet.

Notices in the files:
eib-256/eib-256_panel.brd:
CC BY-SA-NC-4.0
eib-256/eib-generic.sch:
LICENSE: (c) Jon Newman CC-BY-SA-NC 4.0
eib-64-large/eib-64-large.brd:
CERN OHL v1.2
eib-64-large/eib-64-large.sch:
LICENSE: CERN OHL v1.2
